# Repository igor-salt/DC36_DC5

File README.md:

Герберы для Резонита - в папке GERBERS, для JLCPCD - в папке production.
Перечень элементов для информации - в файле DC36_DC5.csv, для загрузки в Платан - в DC36_DC5_PL.csv.
Выгрузка заказа на 10 плат из корзины Платана - platan.xls.
В PNG - скриншоты пробных заказов комплестующих и плат в Платане, Резоните и JLCPCB.

1. При установке подстроечного резистора RV1, не устанавливаются элементы поз. R1 R2 и наоборот.

2. При использовании U1 в исполнении на фиксированное выходное напряжение, не устанавливаются
 элементы поз. R1, R2, RV1, C4, а на место R2 устанавливается перемычка.

3. Посадочные места элементов D1, D2 допускают установку подходящих по параметрам диодов в корпусах
DPAK, D2PAK, SMB, SMC; D4 - SMB, SMC.

4. Посадочные места элементов С2, С5 - допускают установку подходящих по параметрам конденсаторов
в корпусах 8 и 10 мм.

5. Посадочное место L1 позволяет устанавливать дроссели типоразмеров от 10х10 до 18х18.

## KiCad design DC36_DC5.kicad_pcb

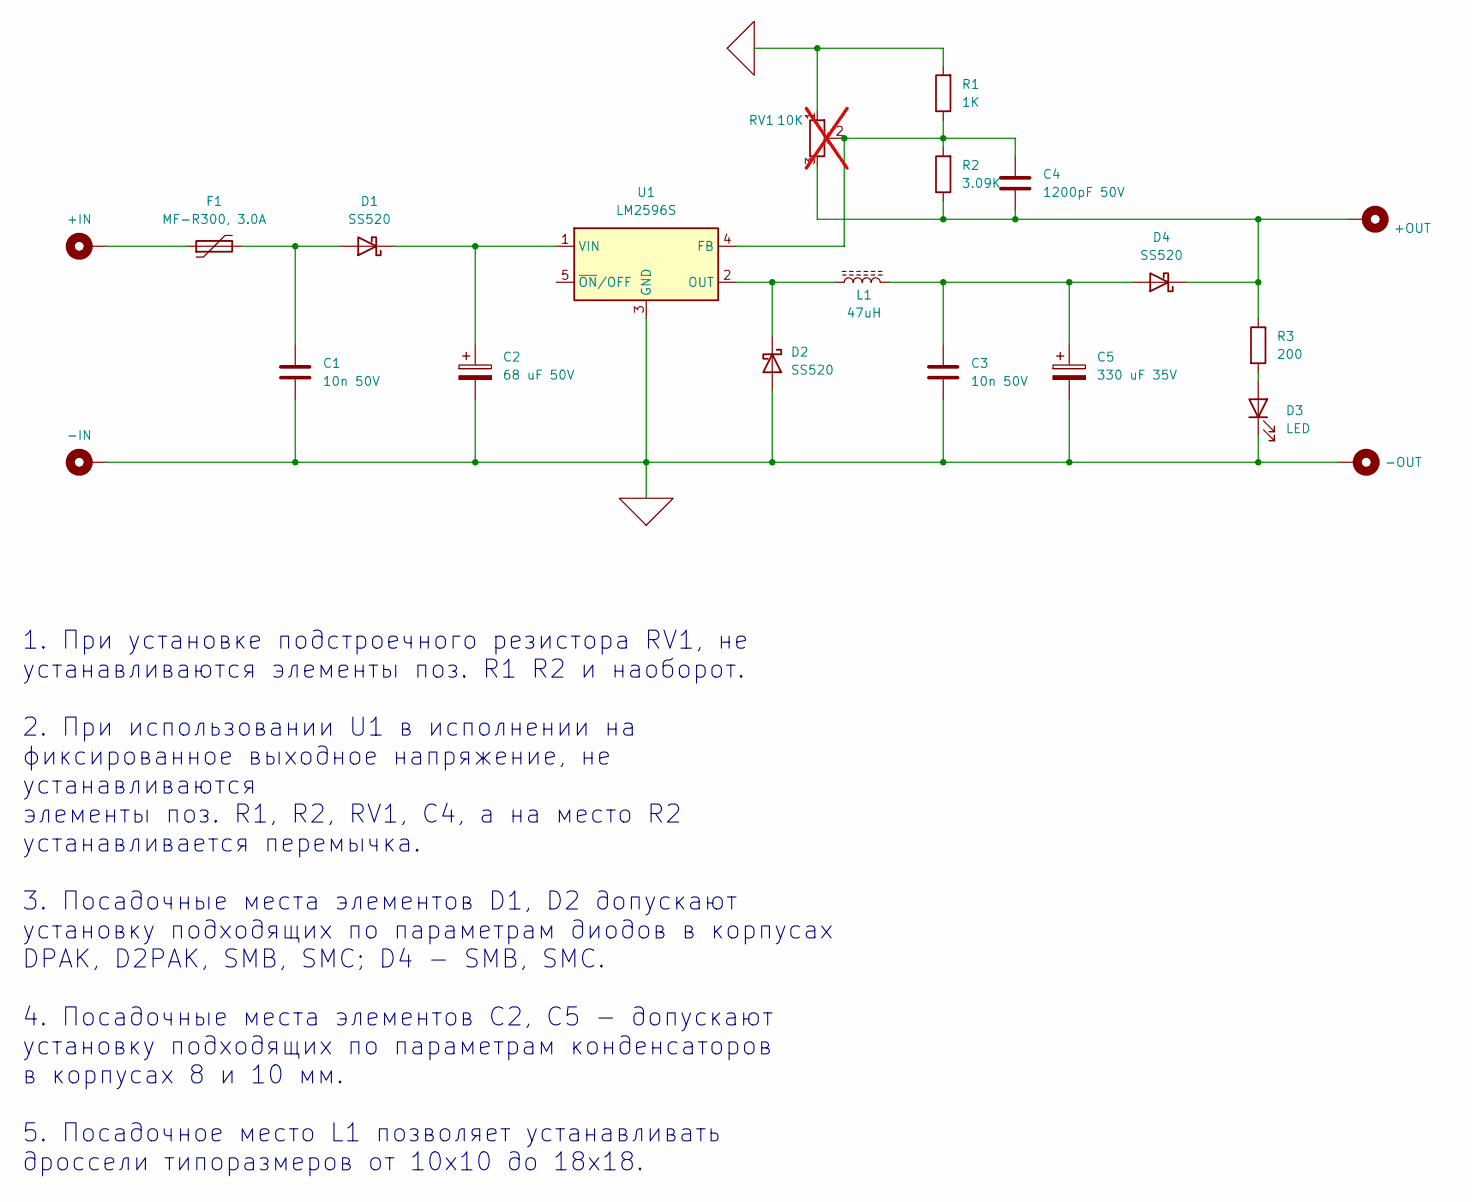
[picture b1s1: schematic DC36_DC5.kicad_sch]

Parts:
C1, C3: 10n 50V; C_0603_1608Metric
C2: 68 uF 50V; CP_Elec_8_10
C4: 1200pF 50V; C_1206_3216Metric
C5: 330 uF 35V; CP_Elec_8_10
D1, D2: SS520; DPAK_DDPAK
D3: LED; LED_0805_2012Metric_Pad1.15x1.40mm_HandSolder
D4: SS520; D_SMB-SMC_Universal_Handsoldering
F1: MF-R300, 3.0A; Fuse_Bourns_MF-R
H1: +IN; MountingHole_3.7x8mm_Pad_Via
H2: -IN; MountingHole_3.7x8mm_Pad_Via
H3: -OUT; MountingHole_3.7x8mm_Pad
H4: +OUT; MountingHole_3.7x8mm_Pad
L1: 47uH; L_10_12.7
R1: 1K; R_0805_2012Metric_Pad1.20x1.40mm_HandSolder
R2: 3.09K; R_0805_2012Metric_Pad1.20x1.40mm_HandSolder
R3: 200; R_0805_2012Metric_Pad1.20x1.40mm_HandSolder
RV1: 10K; Potentiometer_Bourns_3296W_Vertical; not fitted
U1: LM2596S

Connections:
unnamed: C1.1, D1.2 (A), F1.2
unnamed: C2.1, D1.1 (K), U1.1 (VIN)
unnamed: D2.1 (K), L1.1, U1.2 (OUT)
unnamed: D3.2 (A), R3.2
unnamed: C3.1, C5.1, D4.2 (A), L1.2
unnamed: C4.1, D4.1 (K), H4.1, R2.1, R3.1, RV1.3
unnamed: F1.1, H1.1
unnamed: C4.2, R1.1, R2.2, RV1.2, U1.4 (FB)
P,GND: C1.2, C2.2, C3.2, C5.2, D2.2 (A), D3.1 (K), H2.1, H3.1, R1.2, RV1.1, U1.3 (GND)

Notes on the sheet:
1. При установке подстроечного резистора RV1, не устанавливаются элементы поз. R1 R2 и наоборот. 2. При использовании U1 в исполнении на фиксированное выходное напряжение, не устанавливаются элементы поз. R1, R2, RV1, C4, а на место R2 устанавливается перемычка. 3. Посадочные места элементов D1, D2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

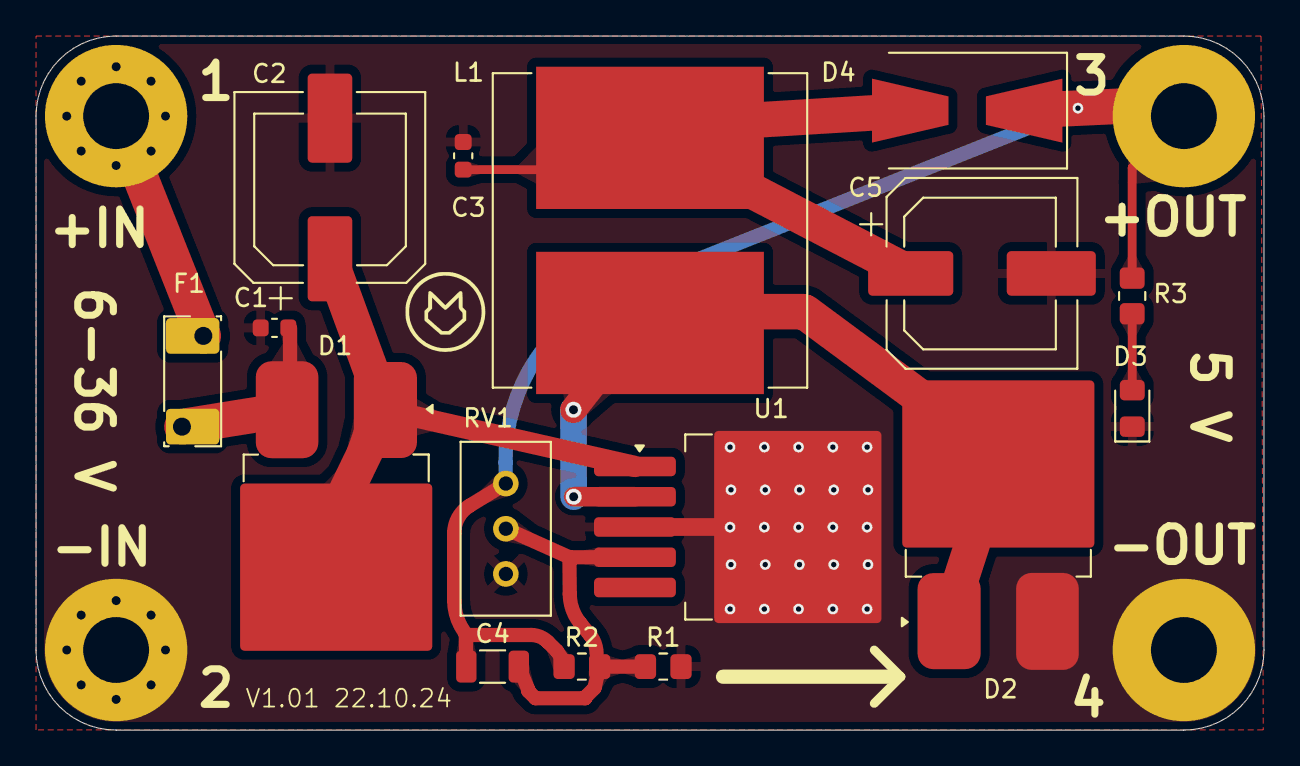
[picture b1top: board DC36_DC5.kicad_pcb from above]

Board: 2 copper layers, 69.0 x 39.0 mm, 21 parts (0 on the bottom side), 9 nets.

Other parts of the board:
ARROW: ARROW

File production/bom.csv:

Designator,Footprint,Quantity,Value,LCSC Part #
"C1, C3",0603,2,10n 50V,
C2,CP_Elec_8_10,1,68 uF 50V,
C4,1206,1,1200pF 50V,
C5,CP_Elec_8_10,1,330 uF 35V,
"D1, D2",DPAK_DDPAK,2,STPS20M100SG,
D3,0805,1,LED,
D4,D_SMB-SMC_Universal_Handsoldering,1,SS56 60V/5A,
F1,Fuse_Bourns_MF-R,1,"MF-R300, 3.0A",
L1,L_10_12.7,1,47uH,
R1,0805,1,1K,
R2,0805,1,3.09K,
R3,0805,1,200,
RV1,Potentiometer_Bourns_3296W_Vertical,1,10K,
U1,LM2596S,1,LM2596S,

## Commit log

2024-10-21 v0.1
2024-10-21 gerbers
2024-10-21 Ver 1.0
2024-10-21 V1.01
2024-10-22 reload
2024-10-22 reorder
2024-10-22 Add dtscription
2024-10-22 To prod
